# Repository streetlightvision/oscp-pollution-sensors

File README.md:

These projects were built to be used with oscp-datalogger.

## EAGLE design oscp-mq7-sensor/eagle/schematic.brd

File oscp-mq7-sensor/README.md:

OSCP Gateway for MQ7 CO Sensor
=====

Work in progress!

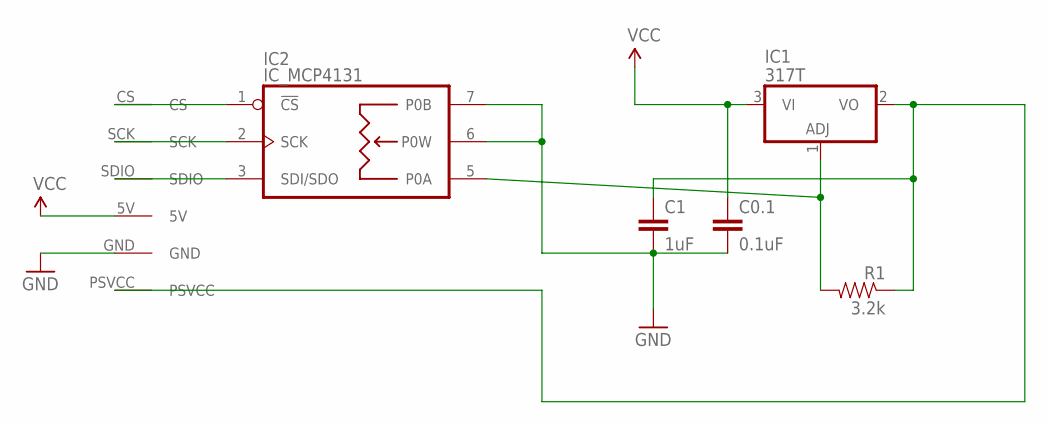
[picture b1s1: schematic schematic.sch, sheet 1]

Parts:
C0.1: 0.1uF; CAP-PTH-SMALL-KIT
C1: 1uF; CAP-PTH-SMALL-KIT
IC1: 317T; TO220H
IC2: IC_MCP4131; DIP8
R1: 3.2k; AXIAL-0.3
U$1: PS_CONNNORMAL; PS_CONN

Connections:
GND: C0.1.2, C1.2, IC2.4 (GND), IC2.6 (P0W), IC2.7 (P0B), U$1.GND
unnamed: IC1.1 (ADJ), IC2.5 (P0A), R1.P$2 (2)
unnamed: IC2.3 (SDI/SDO), U$1.SDIO
unnamed: IC2.2 (SCK), U$1.SCK
unnamed: C1.1, IC1.2 (VO), R1.P$1 (1), U$1.PSVCC
unnamed: IC2.1 (!CS), U$1.CS
VCC: C0.1.1, IC1.3 (VI), IC2.8 (V+), U$1.5V

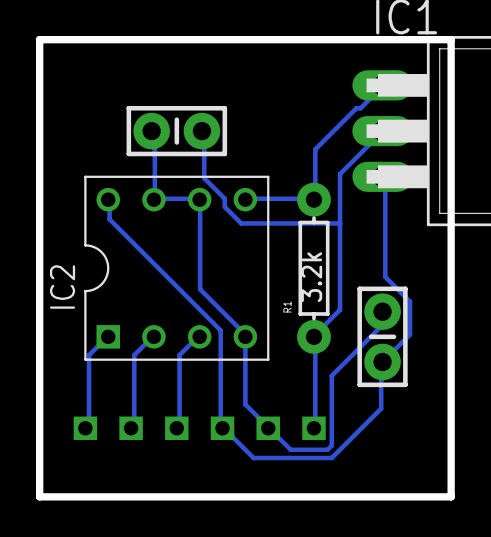
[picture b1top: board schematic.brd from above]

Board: 2 copper layers, 22.9 x 25.4 mm, 6 parts (0 on the bottom side), 7 nets.

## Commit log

2017-06-14 Initial import.

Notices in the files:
parts and their libraries:
SparkFun-Capacitors: Licensing: Creative Commons ShareAlike 4.0 International - https://creativecommons.org/licenses/by-sa/4.0
